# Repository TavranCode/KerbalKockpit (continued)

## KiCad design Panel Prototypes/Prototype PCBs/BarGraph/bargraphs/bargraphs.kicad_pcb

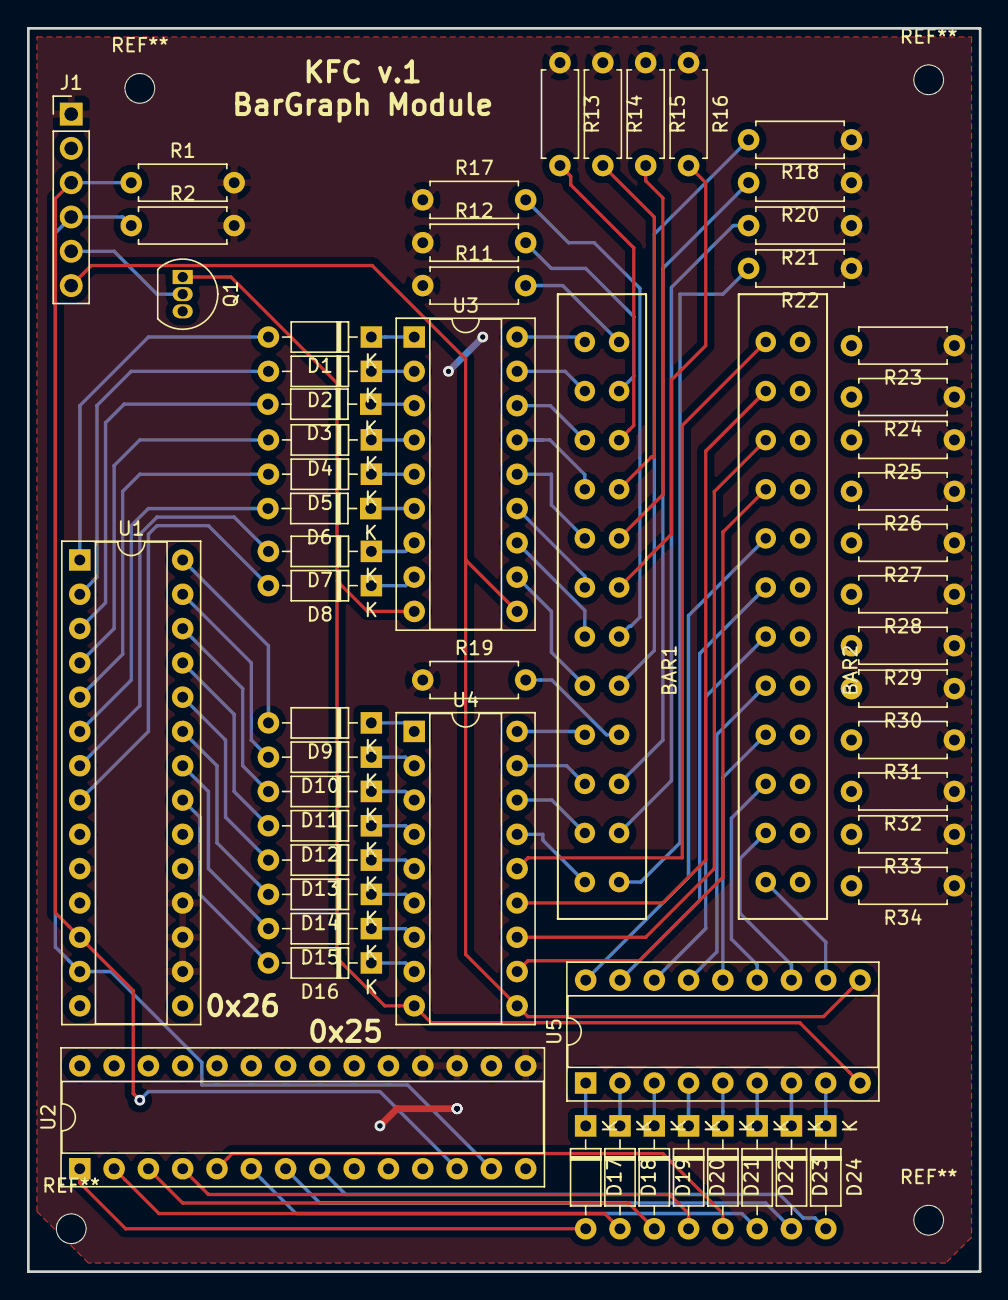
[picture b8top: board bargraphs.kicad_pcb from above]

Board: 2 copper layers, 70.5 x 92.1 mm, 59 parts (0 on the bottom side), 103 nets.

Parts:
BAR1, BAR2: Bargraph.12; BarGraph.12
D1, D2, D3, D4, D5, D6, D7, D8, D9, D10, D11, D12, D13, D14, D15, D16, D17, D18, D19, D20, D21, D22, D23, D24: D; D_DO-35_SOD27_P7.62mm_Horizontal
J1: Conn_01x06; PinHeader_1x06_P2.54mm_Vertical
Q1: 2N3906; TO-92_Inline
R1, R2: 4.7k; R_Axial_DIN0207_L6.3mm_D2.5mm_P7.62mm_Horizontal
R11, R12, R13, R14, R15, R16, R17, R18, R19, R20, R21, R22, R23, R24, R25, R26, R27, R28, R29, R30, R31, R32, R33, R34: 47; R_Axial_DIN0207_L6.3mm_D2.5mm_P7.62mm_Horizontal
U1, U2: MCP23017_SP; DIP-28_W7.62mm_Socket
U3, U4, U5: ULN2803A; DIP-18_W7.62mm_Socket

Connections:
+5V: J1.1, R1.2, R2.2, R11.1, R12.1, R13.1, R14.1, R15.1, R16.1, R17.1, R18.1, R19.1, R20.1, R21.1, R22.1, R23.1, R24.1, R25.1, R26.1, R27.1, R28.1, R29.1, R30.1, R31.1, R32.1, R33.1, R34.1, U1.10, U1.16, U1.17, U1.18, U2.10, U2.15, U2.17, U2.18
/DIM: Q1.1, U3.9, U4.9, U5.9
/LTEST: J1.6, U3.10, U4.10, U5.10
/SCK: J1.3, R1.1, U1.12, U2.12
/SDA: J1.4, R2.1, U1.13, U2.13
/n1: D16.2, U1.21
/n2: D15.2, U1.22
/n3: D14.2, U1.23
/n4: D13.2, U1.24
/n5: D12.2, U1.25
/n6: D11.2, U1.26
/n7: D10.2, U1.27
/n8: D9.2, U1.28
Earth: J1.2, Q1.3, U1.9, U1.15, U2.9, U2.16
unnamed: BAR1.1, U3.18
unnamed: BAR1.2, U3.17
unnamed: BAR1.3, U3.16
unnamed: BAR1.4, U3.15
unnamed: BAR1.5, U3.14
unnamed: BAR1.6, U3.13
unnamed: BAR1.7, U3.12
unnamed: BAR1.8, U3.11
unnamed: BAR1.9, U4.18
unnamed: BAR1.10, U4.17
unnamed: BAR1.11, U4.16
unnamed: BAR1.12, U4.15
unnamed: BAR1.13, R22.2
unnamed: BAR1.14, R21.2
unnamed: BAR1.15, R20.2
unnamed: BAR1.16, R19.2
unnamed: BAR1.17, R18.2
unnamed: BAR1.18, R17.2
unnamed: BAR1.19, R16.2
unnamed: BAR1.20, R15.2
unnamed: BAR1.21, R14.2
unnamed: BAR1.22, R13.2
unnamed: BAR1.23, R12.2
unnamed: BAR1.24, R11.2
unnamed: BAR2.1, U4.14
unnamed: BAR2.2, U4.13
unnamed: BAR2.3, U4.12
unnamed: BAR2.4, U4.11
unnamed: BAR2.5, U5.18
unnamed: BAR2.6, U5.17
unnamed: BAR2.7, U5.16
unnamed: BAR2.8, U5.15
unnamed: BAR2.9, U5.14
unnamed: BAR2.10, U5.13
unnamed: BAR2.11, U5.12
unnamed: BAR2.12, U5.11
unnamed: BAR2.13, R34.2
unnamed: BAR2.14, R33.2
unnamed: BAR2.15, R32.2
unnamed: BAR2.16, R31.2
unnamed: BAR2.17, R30.2
unnamed: BAR2.18, R29.2
unnamed: BAR2.19, R28.2
unnamed: BAR2.20, R27.2
unnamed: BAR2.21, R26.2
unnamed: BAR2.22, R25.2
unnamed: BAR2.23, R24.2
unnamed: BAR2.24, R23.2
unnamed: D1.1, U3.1
unnamed: D1.2, U1.1
unnamed: D2.1, U3.2
unnamed: D2.2, U1.2
unnamed: D3.1, U3.3
unnamed: D3.2, U1.3
unnamed: D4.1, U3.4
unnamed: D4.2, U1.4
unnamed: D5.1, U3.5
unnamed: D5.2, U1.5
unnamed: D6.1, U3.6
unnamed: D6.2, U1.6
unnamed: D7.1, U3.7
unnamed: D7.2, U1.7
unnamed: D8.1, U3.8
unnamed: D8.2, U1.8
unnamed: D9.1, U4.1
unnamed: D10.1, U4.2
unnamed: D11.1, U4.3
unnamed: D12.1, U4.4
unnamed: D13.1, U4.5
unnamed: D14.1, U4.6
unnamed: D15.1, U4.7
unnamed: D16.1, U4.8
unnamed: D17.1, U5.1
unnamed: D17.2, U2.1
unnamed: D18.1, U5.2
unnamed: D18.2, U2.2
unnamed: D19.1, U5.3
unnamed: D19.2, U2.3
unnamed: D20.1, U5.4
unnamed: D20.2, U2.4
unnamed: D21.1, U5.5
unnamed: D21.2, U2.5
unnamed: D22.1, U5.6
unnamed: D22.2, U2.6
unnamed: D23.1, U5.7
unnamed: D23.2, U2.7
unnamed: D24.1, U5.8
unnamed: D24.2, U2.8
unnamed: J1.5, Q1.2

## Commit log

2016-08-02 :circus_tent: Added .gitattributes
2016-08-02 Initial Upload
    Initial upload of all SW and Docs done to date
2016-08-02 Getting rid of PYCharm files
2016-08-02 Still trying to get rid of pycharm files
2016-08-03 removing pycharm files
2016-08-05 Fixed power off and serial out issues
2016-08-05 Updated Documentation and Schematics
    Commenced design doc and added I2C Pull Up resistors.
2016-08-07 Update do design notes
2016-08-07 Various GUI Updates
    Started adding data to GUI Tab 2, which required more data from the
    Arduino
2016-08-09 Implemented subframes as a class
    Used a subframe class to greatly simplify code for the GUI, plus general
    tidy ups
2016-08-09 Implemented subframes as a class
2016-08-15 GUI Updates
    Adding a lot of GUI features plus
    - tolerance on CNIA for throttle
    - changed the sub process start to allow run without panel and reconnect
    - lots of python code cleanup
2016-08-15 SAS Overide
    Disable SAS when the pitch controller is in use. SAS tries to filter out
    the inputs and then overcompensates when you release. On release of the
    controller SAS re-engages automatically
2016-08-15 Added more GUI stuff
    Landing is a copy of launch for now, and added Rondezvous data which is
    wobly as orbits are unstable. Also slowed down the GUI.
2016-08-20 Documentation Updates
    Documented Arduino Code and added electrical grounding descriptions.
    Alse fixed a type in an arduino file but it has no real effect.
2016-08-27 GUI update and plots
    A lot of GUI changes, particularly moving from grid to pack layouts.
    Also added matplotlib plots to a number of pages. Orbit plot still a WIP
2016-10-02 GUI Update
    Improved plots with switching built in, and add frame timing to GUI for
    consistent behaviour. A lot of performance updates.
2016-10-02 Autopilot Panel
    Major update to integrate autopilot panel. Note not all drawings and
    docs are updated yet! And the Python side is not ready for it. (should
    have done this as a branch!)
2016-10-13 AP Panel Improvements
    Added a fastmode to value setting if you hold the button down, and setup
    ability for selected modes to wrap values, e.g. heading
2016-10-13 Documentation Updates
    Updated data file for new data transfers for AP, and updated schematics
    to show AP panel
2016-10-13 Autopilot and KRPC 3.6
    Added AP interface to Arduino, updated GUI to show AP data and button
    maint data. Setup first basic AP code (WIP). Updated for KRPC 3.6.
2018-09-26 commented or removed unused, started CNIA exception handling
2018-09-26 Added accessories
2018-10-01 Added CNIA timeout error
2018-10-01 cleaned up bad debug code
2019-02-11 Lots of revisions
2019-10-11 Uploaded test projects and prototypes to date
2019-10-11 Labels File
2020-02-17 V2 Panels. Matrix Input Test Sketch
2020-03-09 Corrected Unavailable 74HC4051 footprint on Shield Board
2020-03-09 fixed zipfile
2020-07-04 Catch Up
2020-07-04 Commit old controller code pre-32u4 revision
2020-07-27 updated testing scripts
